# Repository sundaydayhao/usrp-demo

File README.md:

# USRP1 七款子板 KiCad 工程

## Windows 实机诊断与 IQ 采集

2026-09-28 合入本地 Windows 项目的安装、硬件排查和接收实验资料，完整记录见 [Windows 安装与诊断记录](WINDOWS_DIAGNOSTICS.md)。

- `scripts/`：诊断、EEPROM 读取、IQ 采集与离线绘图脚本；Python 依赖见 `requirements.txt`。
- `logs/`：诊断日志、EEPROM 备份、原始 sc16 IQ 数据及采集参数。
- `plots/`：频谱、时频图、CSV 和分析结果。
- `downloads/`：排查时使用的参考源码、原理图、器件资料与 USB 驱动文件。

本地虚拟环境、Python 缓存、UHD 安装包、解压工具目录和上游完整文件列表未提交；这些文件仍保留在本机。原始 IQ 录制及已有的采样溢出、时钟配置等限制详见诊断记录。

## KiCad 子板工程

按用户提供资料重建，每款一个独立工程。BasicRX 与 RXMOD、BasicTX 与 TXMOD 分别合并，不重复交付。所有工程保留 USRP1 接口。

2026-09-14 更新：七个工程的 8 颗 EEPROM 全部改为 **AT24C02（Microchip AT24C02C-SSHM-T / C6203）**，同步原理图、PCB 和 BOM。阻容感支持按价格与供货选择国内或国际品牌；本次锁定 12 颗国巨电阻和 38 颗三星去耦电容。详见 [器件更新说明与采购快照](COMPONENT_UPDATE.md)，EEPROM 页写长度为 8 字节。

| 工程 | 原理图 | PCB | ERC 错误 | DRC 错误 | 未连接 |
|---|---|---|---:|---:|---:|
| [BasicRX](projects/BasicRX/BasicRX.kicad_pro) | [原理图](projects/BasicRX/BasicRX.kicad_sch) | [PCB](projects/BasicRX/BasicRX.kicad_pcb) | 0 | 0 | 0 |
| [BasicTX](projects/BasicTX/BasicTX.kicad_pro) | [原理图](projects/BasicTX/BasicTX.kicad_sch) | [PCB](projects/BasicTX/BasicTX.kicad_pcb) | 0 | 0 | 0 |
| [LFRX](projects/LFRX/LFRX.kicad_pro) | [原理图](projects/LFRX/LFRX.kicad_sch) | [PCB](projects/LFRX/LFRX.kicad_pcb) | 0 | 0 | 0 |
| [LFTX](projects/LFTX/LFTX.kicad_pro) | [原理图](projects/LFTX/LFTX.kicad_sch) | [PCB](projects/LFTX/LFTX.kicad_pcb) | 0 | 0 | 0 |
| [TVRX](projects/TVRX/TVRX.kicad_pro) | [原理图](projects/TVRX/TVRX.kicad_sch) | [PCB](projects/TVRX/TVRX.kicad_pcb) | 0 | 0 | 0 |
| [TVRX2](projects/TVRX2/TVRX2.kicad_pro) | [原理图](projects/TVRX2/TVRX2.kicad_sch) | [PCB](projects/TVRX2/TVRX2.kicad_pcb) | 0 | 0 | 0 |
| [WBX](projects/WBX/WBX.kicad_pro) | [原理图](projects/WBX/WBX.kicad_sch) | [PCB](projects/WBX/WBX.kicad_pcb) | 0 | 0 | 0 |

检查状态来自 `verification/<工程名>/final-summary.json`，只说明 CAD 文件在记录时通过了哪些检查。完整说明见 [DESIGN_NOTES.md](DESIGN_NOTES.md)。

每个目录自带符号、封装、库表、采购 BOM 与预览。用 KiCad 10 打开 `.kicad_pro` 即可编辑。WBX/TVRX2 为按公开资料重新设计的 PCB，射频指标、机械插接和上电功能仍需样板验证；WBX 的 LO 变压器频率裕量、TVRX2 的 CPLD 编程文件尚未通过实物验证。

五款旧板从历史 gEDA CAD 恢复；两款复杂板从 PDF 重建。具体版本、数值差异、器件替代和工艺约束均在设计说明中列出。

WBX 为自定义六层，另外六款为四层；六层的板厂压合与阻抗确认是打样前的必要工作。检查报告保留孤立标签及历史铜线末端等警告，零错误不表示没有警告。

[审查记录](REVIEW.md)列出检查覆盖范围与未验证项目。

## 3D 模型更新

七个工程现有 578 个模型绑定（新增 198 个），全部使用工程内相对路径，并同步至本地封装库。已核对正反面预览，电路和 RF 走线保持不变。PMC 插座与 TVRX 调谐模块采用明确标注的简化外形，机械尺寸限制见 [3D 模型说明](3D_MODELS.md)。

[七款板 3D 预览 PDF](deliverables/3D-previews.pdf) · [完整工程包](deliverables/USRP1-seven-KiCad-projects.zip)

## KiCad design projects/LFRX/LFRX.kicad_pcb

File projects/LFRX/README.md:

# LFRX

低频接收板，保留模拟前端和差分输出滤波网络。

使用 KiCad 10.0.5 验证。打开 `LFRX.kicad_pro`，工程内包含可编辑原理图、PCB、`USRP.kicad_sym`、`USRP.pretty` 和本地库表。多页工程从同名顶层原理图进入。

ERC 错误 0，ERC 警告 6；DRC 错误 0，DRC 警告 8，未连接 0。详见检查报告。

- [采购 BOM](BOM-sourcing.csv)：实际 LCSC 编码仅在已核对型号与封装时填写；空白项仍需选型/询价。
- [预览](preview/)：原理图和 PCB 各铜层图。
- [完整设计说明](../../DESIGN_NOTES.md)：原始资料差异、USRP1 机械接口、RF 匹配、叠层、装配和样板验证限制。
- [检查证据](../../verification/LFRX/)：ERC、DRC、网表、封装与射频检查记录。

必须连同设计说明审查。TVRX2/WBX 使用焊盘内过孔，应评审塞孔盖铜工艺。PCB 上无源器件位号可在 F.Fab/B.Fab 装配层查看。未进行实物功能或射频指标测试。

## 3D 模型

PCB 和本地封装库已绑定工程内的 `3dmodels/`，无需额外安装模型库。请保留整个工程目录。

- [正反面 3D 预览](preview/3d-views.pdf)
- [模型来源、简化模型与尺寸限制](../../3D_MODELS.md)

PMC 插座是简化外形模型；TVRX 的调谐模块也为简化外形，高度按 15 mm 示意，未包含外接 F 连接器。3D 外形补充没有修改电路、焊盘或 RF 走线。

## 2026-09-14 器件更新

EEPROM 已改为 AT24C02，完整料号 Microchip AT24C02C-SSHM-T（C6203）；编程页长 8 字节，不可跨页写入。原有 SOIC-8 焊盘和 3D 模型沿用。阻容感允许按价格、库存和交期选择国内或国际品牌，具体已选料号及待锁定行见本工程 BOM-sourcing.csv；更新证据见 [器件更新说明](../../COMPONENT_UPDATE.md)。

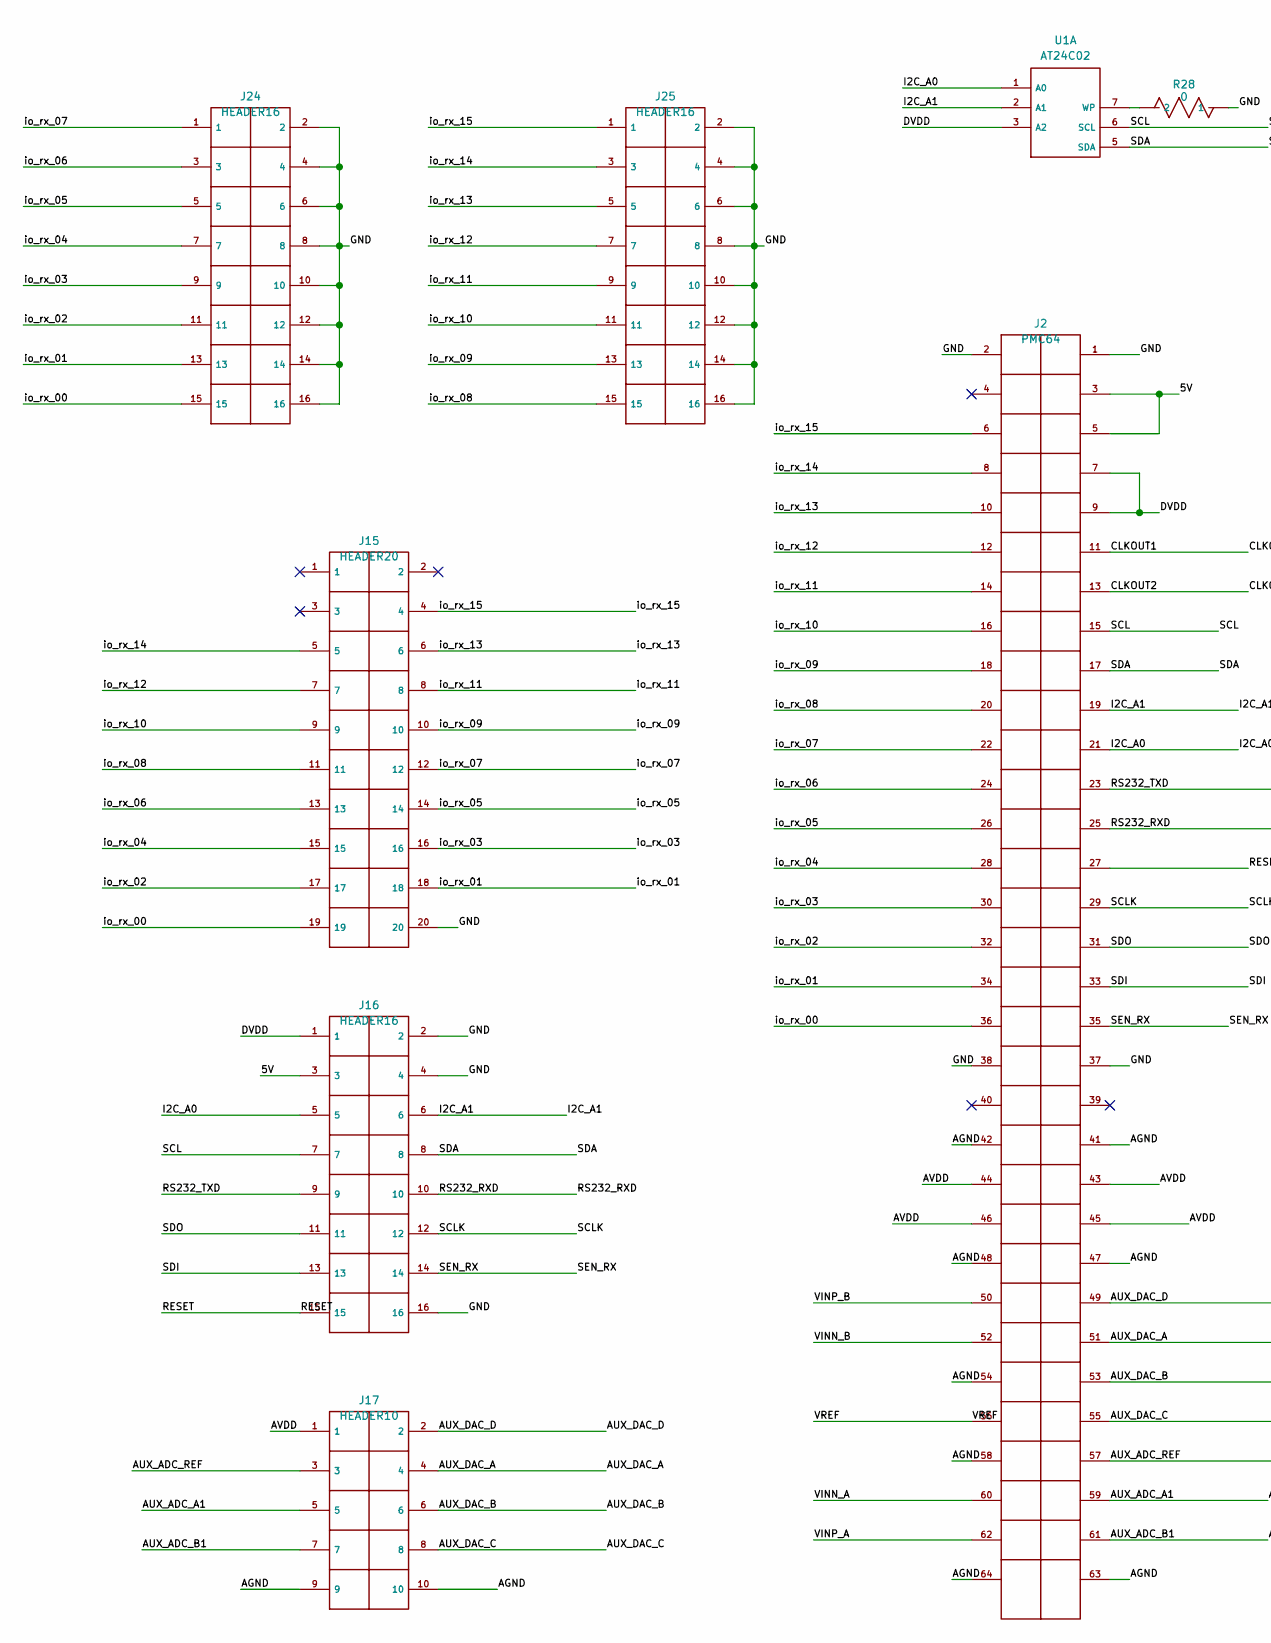
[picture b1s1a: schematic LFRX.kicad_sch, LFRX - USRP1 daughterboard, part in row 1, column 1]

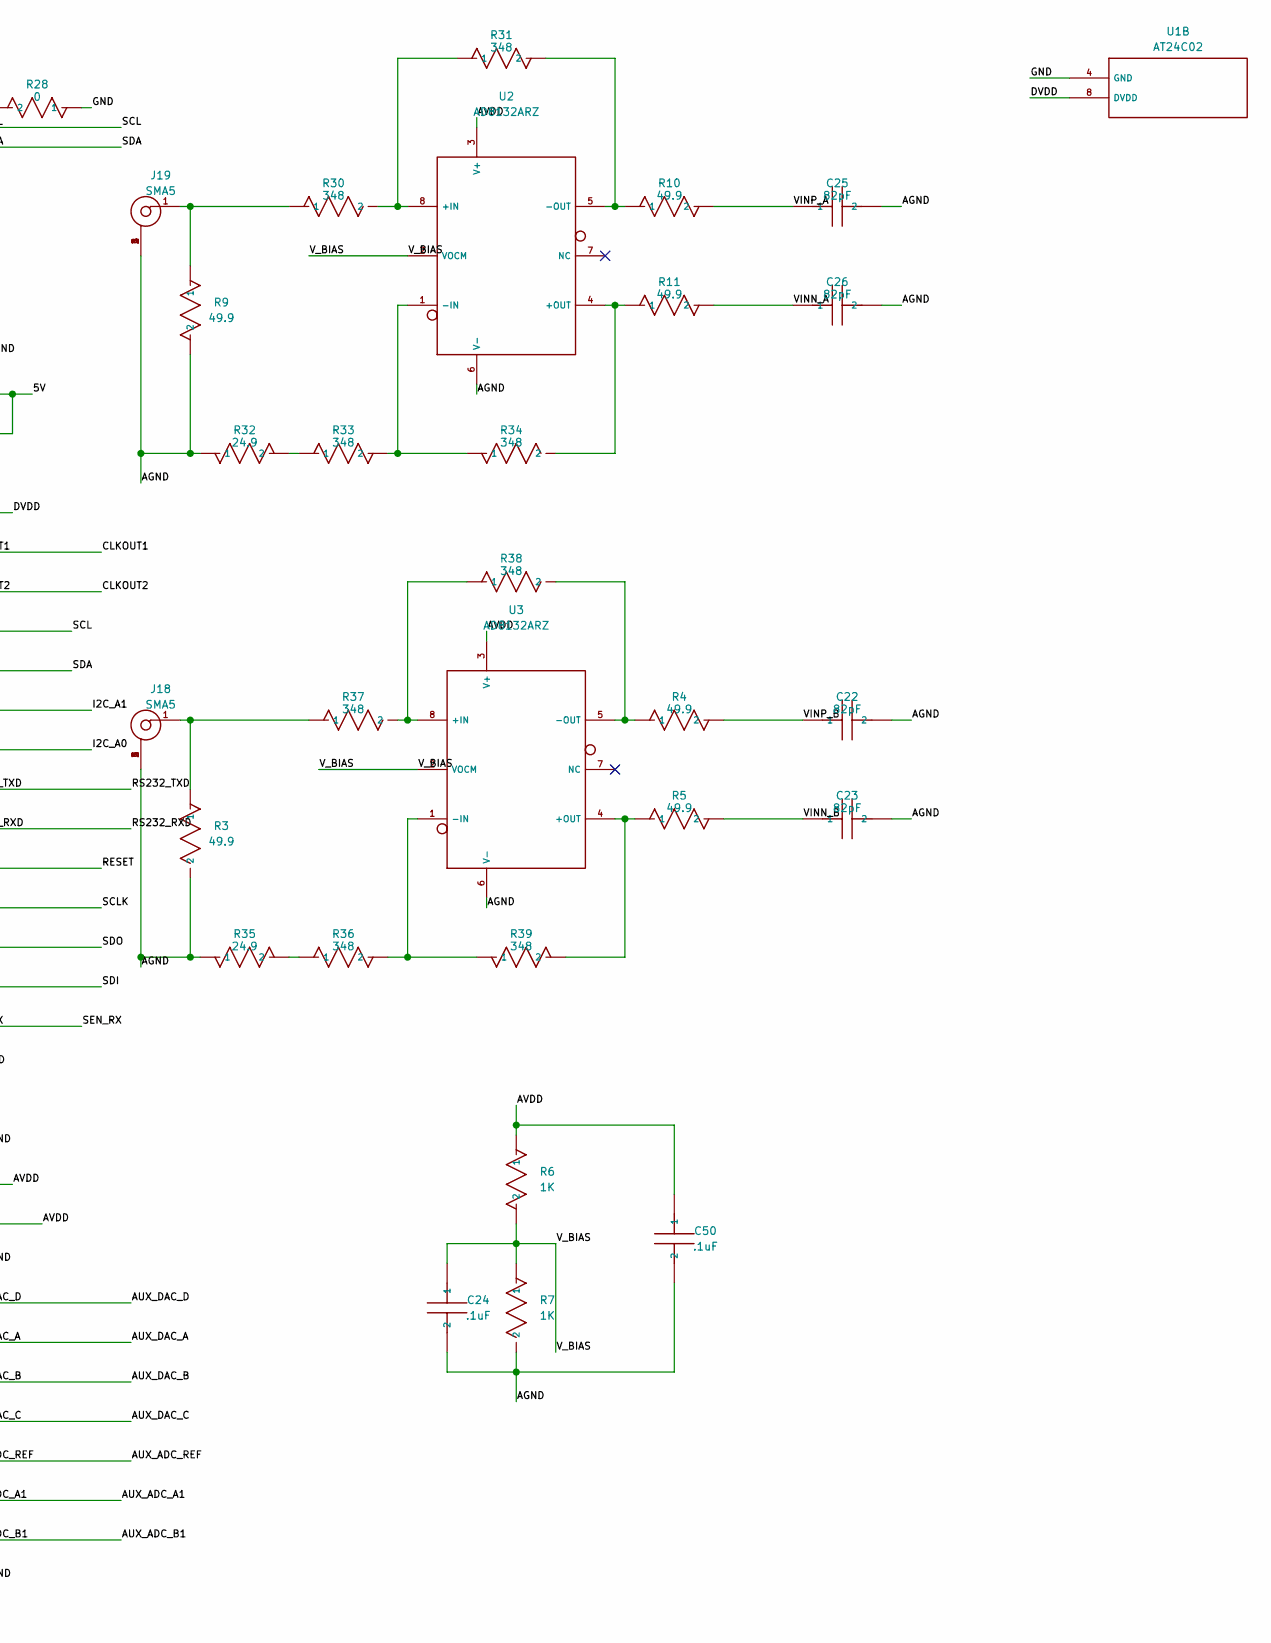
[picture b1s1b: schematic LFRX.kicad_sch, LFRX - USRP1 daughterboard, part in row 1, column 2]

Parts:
C22: 82pF; C22
C23: 82pF; C23
C24: .1uF; C24
C25: 82pF; C25
C26: 82pF; C26
C50: .1uF; C50
J2: PMC64; J2
J15: HEADER20; J15
J16: HEADER16; J16
J17: HEADER10; J17
J18: SMA5; J18
J19: SMA5; J19
J24: HEADER16; J24
J25: HEADER16; J25
R3: 49.9; R3
R4: 49.9; R4
R5: 49.9; R5
R6: 1K; R6
R7: 1K; R7
R9: 49.9; R9
R10: 49.9; R10
R11: 49.9; R11
R28: 0; R28; MPN 0603WAF0000T5E; LCSC C21189
R30: 348; R30
R31: 348; R31
R32: 24.9; R32
R33: 348; R33
R34: 348; R34
R35: 24.9; R35
R36: 348; R36
R37: 348; R37
R38: 348; R38
R39: 348; R39
U1: AT24C02; U1; MPN AT24C02C-SSHM-T; LCSC C6203
U2: AD8132ARZ; U2; MPN AD8132ARZ
U3: AD8132ARZ; U3; MPN AD8132ARZ

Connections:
/5V: J2.3, J2.5, J16.3
/AGND: C22.2, C23.2, C24.2, C25.2, C26.2, C50.2, J2.41, J2.42, J2.47, J2.48, J2.54, J2.58, J2.63, J2.64, J17.9, J17.10, J18.2, J18.3, J18.4, J18.5, J19.2, J19.3, J19.4, J19.5, R3.2, R7.2, R9.2, R32.1, R35.1, U2.6 (V-), U3.6 (V-)
/AUX_ADC_A1: J2.59, J17.5
/AUX_ADC_B1: J2.61, J17.7
/AUX_ADC_REF: J2.57, J17.3
/AUX_DAC_A: J2.51, J17.4
/AUX_DAC_B: J2.53, J17.6
/AUX_DAC_C: J2.55, J17.8
/AUX_DAC_D: J2.49, J17.2
/AVDD: C50.1, J2.43, J2.44, J2.45, J2.46, J17.1, R6.1, U2.3 (V+), U3.3 (V+)
/CLKOUT1: J2.11
/CLKOUT2: J2.13
/DVDD: J2.7, J2.9, J16.1, U1.3 (A2), U1.8 (DVDD)
/GND: J2.1, J2.2, J2.37, J2.38, J15.20, J16.2, J16.4, J16.16, J24.2, J24.4, J24.6, J24.8, J24.10, J24.12, J24.14, J24.16, J25.2, J25.4, J25.6, J25.8, J25.10, J25.12, J25.14, J25.16, R28.1, U1.4 (GND)
/I2C_A0: J2.21, J16.5, U1.1 (A0)
/I2C_A1: J2.19, J16.6, U1.2 (A1)
/RESET: J2.27, J16.15
/RS232_RXD: J2.25, J16.10
/RS232_TXD: J2.23, J16.9
/SCL: J2.15, J16.7, U1.6 (SCL)
/SCLK: J2.29, J16.12
/SDA: J2.17, J16.8, U1.5 (SDA)
/SDI: J2.33, J16.13
/SDO: J2.31, J16.11
/SEN_RX: J2.35, J16.14
/VINN_A: C26.1, J2.60, R11.2
/VINN_B: C23.1, J2.52, R5.2
/VINP_A: C25.1, J2.62, R10.2
/VINP_B: C22.1, J2.50, R4.2
/VREF: J2.56
/V_BIAS: C24.1, R6.2, R7.1, U2.2 (VOCM), U3.2 (VOCM)
/io_rx_00: J2.36, J15.19, J24.15
/io_rx_01: J2.34, J15.18, J24.13
/io_rx_02: J2.32, J15.17, J24.11
/io_rx_03: J2.30, J15.16, J24.9
/io_rx_04: J2.28, J15.15, J24.7
/io_rx_05: J2.26, J15.14, J24.5
/io_rx_06: J2.24, J15.13, J24.3
/io_rx_07: J2.22, J15.12, J24.1
/io_rx_08: J2.20, J15.11, J25.15
/io_rx_09: J2.18, J15.10, J25.13
/io_rx_10: J2.16, J15.9, J25.11
/io_rx_11: J2.14, J15.8, J25.9
/io_rx_12: J2.12, J15.7, J25.7
/io_rx_13: J2.10, J15.6, J25.5
/io_rx_14: J2.8, J15.5, J25.3
/io_rx_15: J2.6, J15.4, J25.1
unnamed: J18.1, R3.1, R37.1
unnamed: J19.1, R9.1, R30.1
unnamed: R32.2, R33.1
unnamed: R35.2, R36.1
unnamed: R28.2, U1.7 (WP)
unnamed: R30.2, R31.1, U2.8 (+IN)
unnamed: R11.1, R34.2, U2.4 (+OUT)
unnamed: R33.2, R34.1, U2.1 (-IN)
unnamed: R10.1, R31.2, U2.5 (-OUT)
unnamed: R37.2, R38.1, U3.8 (+IN)
unnamed: R5.1, R39.2, U3.4 (+OUT)
unnamed: R36.2, R39.1, U3.1 (-IN)
unnamed: R4.1, R38.2, U3.5 (-OUT)

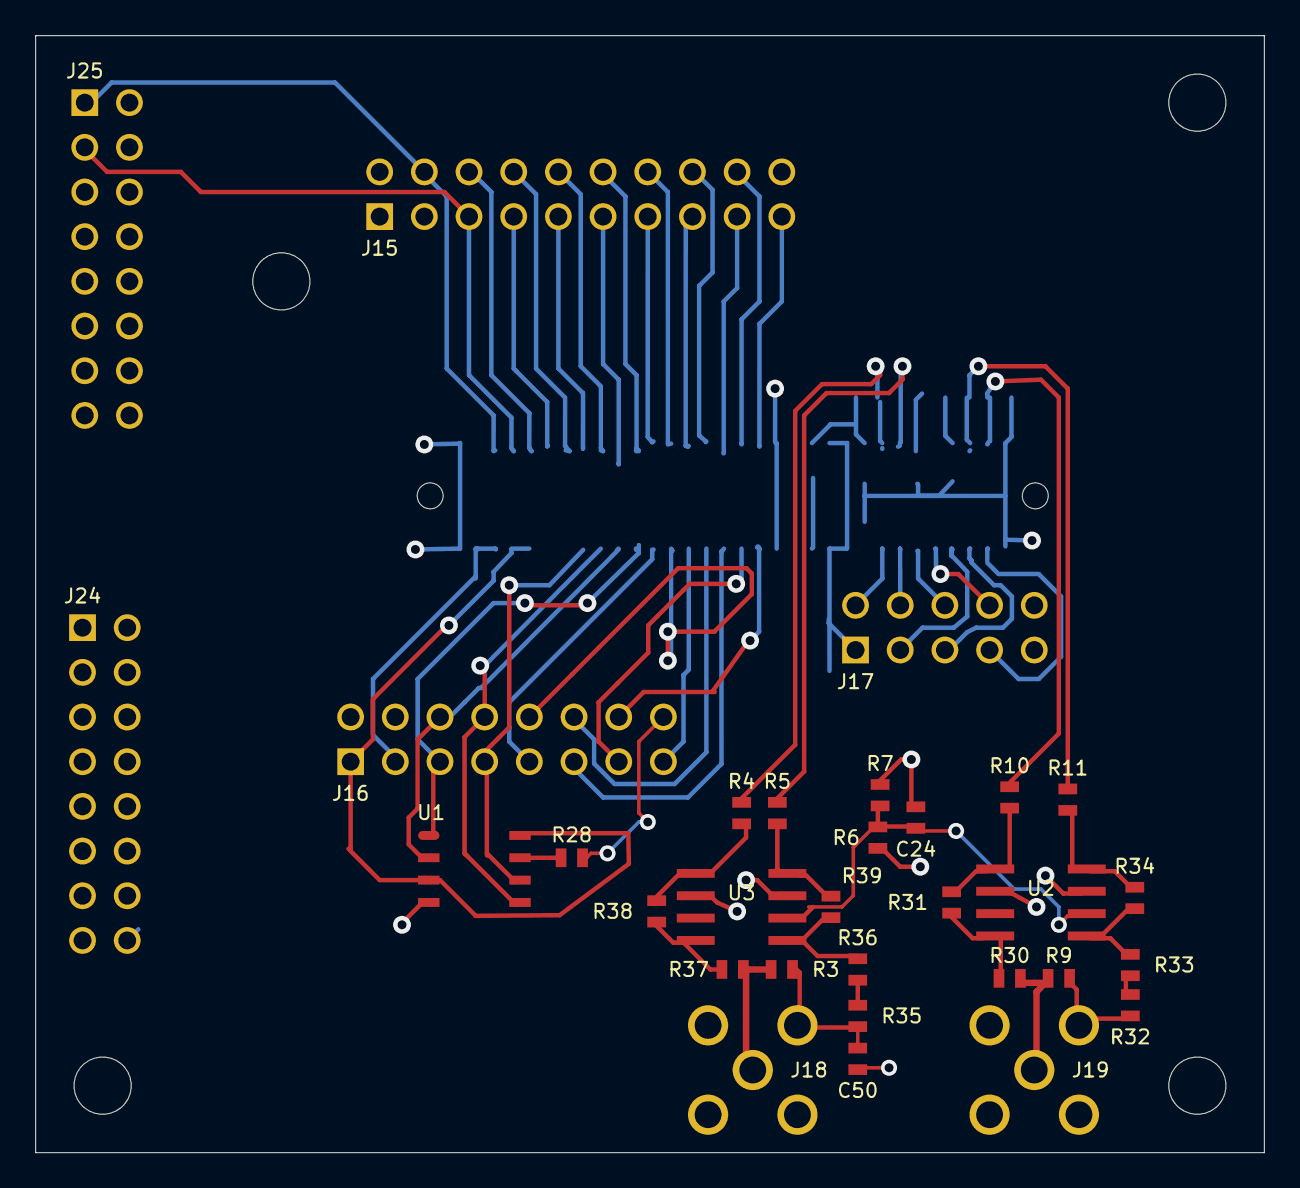
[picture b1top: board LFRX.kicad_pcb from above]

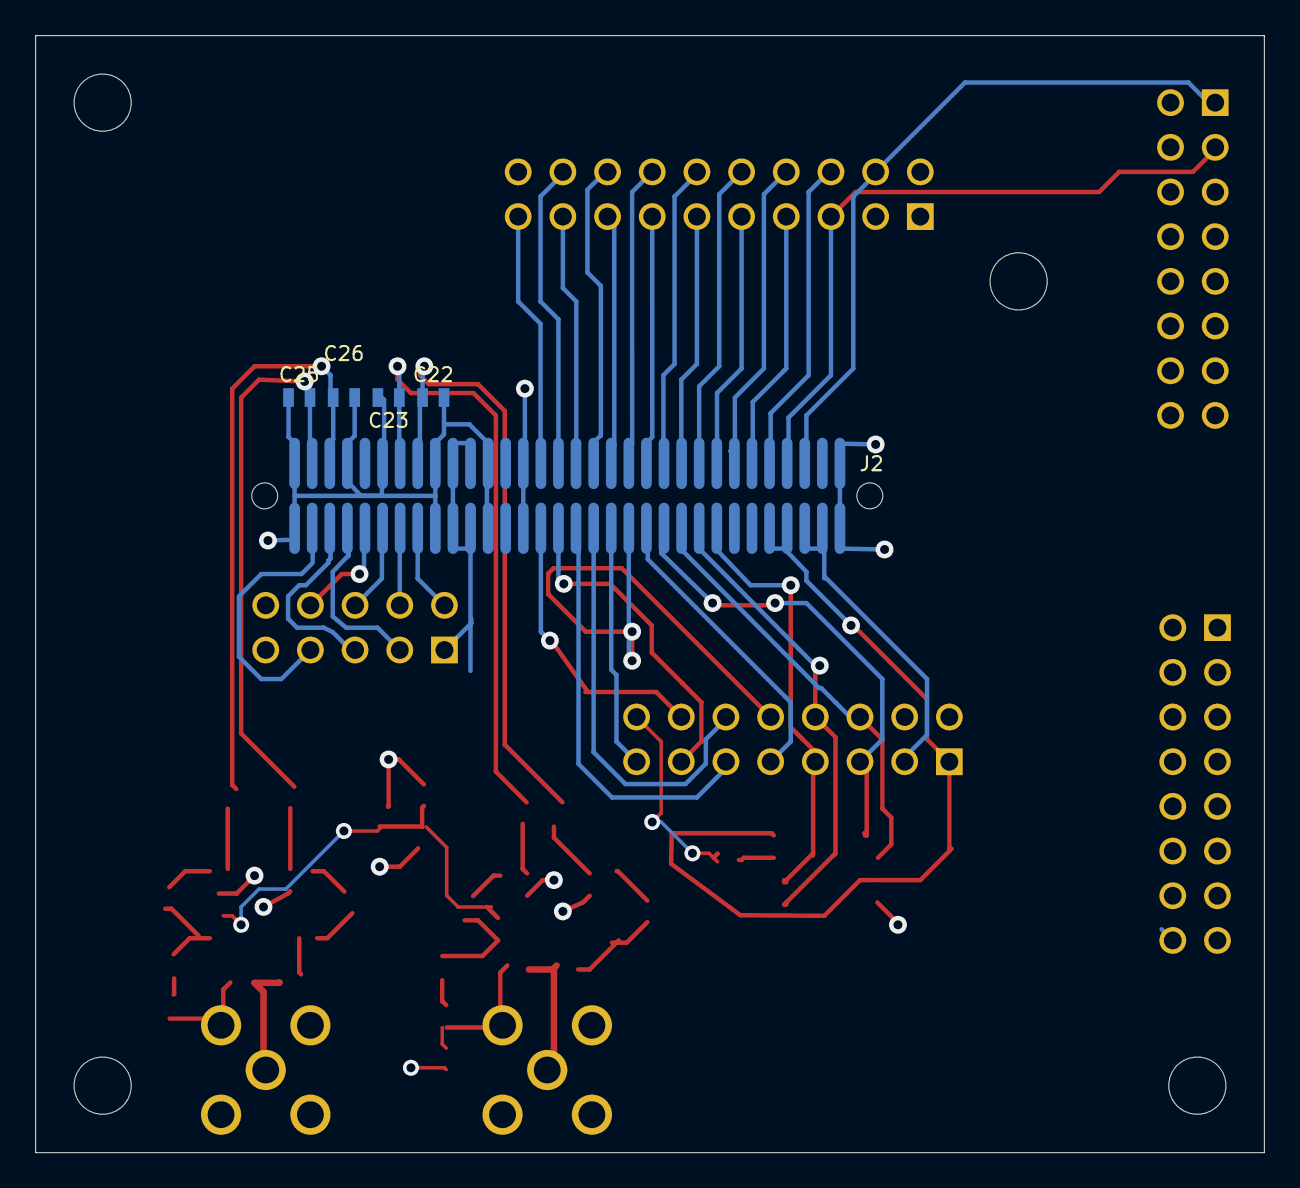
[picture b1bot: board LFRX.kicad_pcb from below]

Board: 4 copper layers, 69.8 x 63.5 mm, 40 parts (5 on the bottom side), 57 nets.

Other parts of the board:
H1, H2, H3, H4: NPTH

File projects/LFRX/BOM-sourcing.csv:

Reference,Value,Footprint,Manufacturer,MPN,LCSC,Sourcing_status,Specification,Source_value,Evidence,Approved_brands,Sourcing_policy
C22,82pF,USRP:C22,候选：Murata / TDK / Samsung Electro-Mechanics / Walsin / FH / EYANG,,,规格选型，待锁定料号,按项目焊盘尺寸；RF/匹配/PLL环路优先 C0G；去耦 X7R；耐压 >=16 V；保留原容差,82pF,,Murata / TDK / Samsung Electro-Mechanics / Walsin / FH / EYANG,国产与国际品牌均可；满足参数后比较含税到手价、起订量、库存和交期；换料须复核封装及电气指标
C23,82pF,USRP:C23,候选：Murata / TDK / Samsung Electro-Mechanics / Walsin / FH / EYANG,,,规格选型，待锁定料号,按项目焊盘尺寸；RF/匹配/PLL环路优先 C0G；去耦 X7R；耐压 >=16 V；保留原容差,82pF,,Murata / TDK / Samsung Electro-Mechanics / Walsin / FH / EYANG,国产与国际品牌均可；满足参数后比较含税到手价、起订量、库存和交期；换料须复核封装及电气指标
C24,.1uF,USRP:C24,候选：Murata / TDK / Samsung Electro-Mechanics / Walsin / FH / EYANG,,,规格选型，待锁定料号,按项目焊盘尺寸；RF/匹配/PLL环路优先 C0G；去耦 X7R；耐压 >=16 V；保留原容差,.1uF,,Murata / TDK / Samsung Electro-Mechanics / Walsin / FH / EYANG,国产与国际品牌均可；满足参数后比较含税到手价、起订量、库存和交期；换料须复核封装及电气指标
C25,82pF,USRP:C25,候选：Murata / TDK / Samsung Electro-Mechanics / Walsin / FH / EYANG,,,规格选型，待锁定料号,按项目焊盘尺寸；RF/匹配/PLL环路优先 C0G；去耦 X7R；耐压 >=16 V；保留原容差,82pF,,Murata / TDK / Samsung Electro-Mechanics / Walsin / FH / EYANG,国产与国际品牌均可；满足参数后比较含税到手价、起订量、库存和交期；换料须复核封装及电气指标
C26,82pF,USRP:C26,候选：Murata / TDK / Samsung Electro-Mechanics / Walsin / FH / EYANG,,,规格选型，待锁定料号,按项目焊盘尺寸；RF/匹配/PLL环路优先 C0G；去耦 X7R；耐压 >=16 V；保留原容差,82pF,,Murata / TDK / Samsung Electro-Mechanics / Walsin / FH / EYANG,国产与国际品牌均可；满足参数后比较含税到手价、起订量、库存和交期；换料须复核封装及电气指标
C50,.1uF,USRP:C50,候选：Murata / TDK / Samsung Electro-Mechanics / Walsin / FH / EYANG,,,规格选型，待锁定料号,按项目焊盘尺寸；RF/匹配/PLL环路优先 C0G；去耦 X7R；耐压 >=16 V；保留原容差,.1uF,,Murata / TDK / Samsung Electro-Mechanics / Walsin / FH / EYANG,国产与国际品牌均可；满足参数后比较含税到手价、起订量、库存和交期；换料须复核封装及电气指标
J2,PMC64,USRP:J2,,,,规格选型，待锁定料号,按工程封装和 USRP1 接口核对插合方向、针脚与高度,PMC64,,,
J15,HEADER20,USRP:J15,,,,规格选型，待锁定料号,按工程封装和 USRP1 接口核对插合方向、针脚与高度,HEADER20,,,
J16,HEADER16,USRP:J16,,,,规格选型，待锁定料号,按工程封装和 USRP1 接口核对插合方向、针脚与高度,HEADER16,,,
J17,HEADER10,USRP:J17,,,,规格选型，待锁定料号,按工程封装和 USRP1 接口核对插合方向、针脚与高度,HEADER10,,,
J18,SMA5,USRP:J18,,,,规格选型，待锁定料号,按工程封装和 USRP1 接口核对插合方向、针脚与高度,SMA5,,,
J19,SMA5,USRP:J19,,,,规格选型，待锁定料号,按工程封装和 USRP1 接口核对插合方向、针脚与高度,SMA5,,,
J24,HEADER16,USRP:J24,,,,规格选型，待锁定料号,按工程封装和 USRP1 接口核对插合方向、针脚与高度,HEADER16,,,
J25,HEADER16,USRP:J25,,,,规格选型，待锁定料号,按工程封装和 USRP1 接口核对插合方向、针脚与高度,HEADER16,,,
R3,49.9,USRP:R3,候选：YAGEO / Vishay / Panasonic / UNI-ROYAL / FH,,,规格选型，待锁定料号,0603; <=1%; >=0.1 W; 按原值采购；反馈/终端电阻需同批次,49.9,,YAGEO / Vishay / Panasonic / UNI-ROYAL / FH,国产与国际品牌均可；满足参数后比较含税到手价、起订量、库存和交期；换料须复核封装及电气指标
R4,49.9,USRP:R4,候选：YAGEO / Vishay / Panasonic / UNI-ROYAL / FH,,,规格选型，待锁定料号,0603; <=1%; >=0.1 W; 按原值采购；反馈/终端电阻需同批次,49.9,,YAGEO / Vishay / Panasonic / UNI-ROYAL / FH,国产与国际品牌均可；满足参数后比较含税到手价、起订量、库存和交期；换料须复核封装及电气指标
R5,49.9,USRP:R5,候选：YAGEO / Vishay / Panasonic / UNI-ROYAL / FH,,,规格选型，待锁定料号,0603; <=1%; >=0.1 W; 按原值采购；反馈/终端电阻需同批次,49.9,,YAGEO / Vishay / Panasonic / UNI-ROYAL / FH,国产与国际品牌均可；满足参数后比较含税到手价、起订量、库存和交期；换料须复核封装及电气指标
R6,1K,USRP:R6,候选：YAGEO / Vishay / Panasonic / UNI-ROYAL / FH,,,规格选型，待锁定料号,0603; <=1%; >=0.1 W; 按原值采购；反馈/终端电阻需同批次,1K,,YAGEO / Vishay / Panasonic / UNI-ROYAL / FH,国产与国际品牌均可；满足参数后比较含税到手价、起订量、库存和交期；换料须复核封装及电气指标
R7,1K,USRP:R7,候选：YAGEO / Vishay / Panasonic / UNI-ROYAL / FH,,,规格选型，待锁定料号,0603; <=1%; >=0.1 W; 按原值采购；反馈/终端电阻需同批次,1K,,YAGEO / Vishay / Panasonic / UNI-ROYAL / FH,国产与国际品牌均可；满足参数后比较含税到手价、起订量、库存和交期；换料须复核封装及电气指标
R9,49.9,USRP:R9,候选：YAGEO / Vishay / Panasonic / UNI-ROYAL / FH,,,规格选型，待锁定料号,0603; <=1%; >=0.1 W; 按原值采购；反馈/终端电阻需同批次,49.9,,YAGEO / Vishay / Panasonic / UNI-ROYAL / FH,国产与国际品牌均可；满足参数后比较含税到手价、起订量、库存和交期；换料须复核封装及电气指标
R10,49.9,USRP:R10,候选：YAGEO / Vishay / Panasonic / UNI-ROYAL / FH,,,规格选型，待锁定料号,0603; <=1%; >=0.1 W; 按原值采购；反馈/终端电阻需同批次,49.9,,YAGEO / Vishay / Panasonic / UNI-ROYAL / FH,国产与国际品牌均可；满足参数后比较含税到手价、起订量、库存和交期；换料须复核封装及电气指标
R11,49.9,USRP:R11,候选：YAGEO / Vishay / Panasonic / UNI-ROYAL / FH,,,规格选型，待锁定料号,0603; <=1%; >=0.1 W; 按原值采购；反馈/终端电阻需同批次,49.9,,YAGEO / Vishay / Panasonic / UNI-ROYAL / FH,国产与国际品牌均可；满足参数后比较含税到手价、起订量、库存和交期；换料须复核封装及电气指标
R28,0,USRP:R28,UNI-ROYAL 厚声,0603WAF0000T5E,C21189,已核对目录料号,0603; <=1%; >=0.1 W; 按原值采购；反馈/终端电阻需同批次,0,https://www.lcsc.com/product-detail/C21189.html,YAGEO / Vishay / Panasonic / UNI-ROYAL / FH,国产与国际品牌均可；满足参数后比较含税到手价、起订量、库存和交期；换料须复核封装及电气指标
R30,348,USRP:R30,候选：YAGEO / Vishay / Panasonic / UNI-ROYAL / FH,,,规格选型，待锁定料号,0603; <=1%; >=0.1 W; 按原值采购；反馈/终端电阻需同批次,348,,YAGEO / Vishay / Panasonic / UNI-ROYAL / FH,国产与国际品牌均可；满足参数后比较含税到手价、起订量、库存和交期；换料须复核封装及电气指标
R31,348,USRP:R31,候选：YAGEO / Vishay / Panasonic / UNI-ROYAL / FH,,,规格选型，待锁定料号,0603; <=1%; >=0.1 W; 按原值采购；反馈/终端电阻需同批次,348,,YAGEO / Vishay / Panasonic / UNI-ROYAL / FH,国产与国际品牌均可；满足参数后比较含税到手价、起订量、库存和交期；换料须复核封装及电气指标
R32,24.9,USRP:R32,候选：YAGEO / Vishay / Panasonic / UNI-ROYAL / FH,,,规格选型，待锁定料号,0603; <=1%; >=0.1 W; 按原值采购；反馈/终端电阻需同批次,24.9,,YAGEO / Vishay / Panasonic / UNI-ROYAL / FH,国产与国际品牌均可；满足参数后比较含税到手价、起订量、库存和交期；换料须复核封装及电气指标
R33,348,USRP:R33,候选：YAGEO / Vishay / Panasonic / UNI-ROYAL / FH,,,规格选型，待锁定料号,0603; <=1%; >=0.1 W; 按原值采购；反馈/终端电阻需同批次,348,,YAGEO / Vishay / Panasonic / UNI-ROYAL / FH,国产与国际品牌均可；满足参数后比较含税到手价、起订量、库存和交期；换料须复核封装及电气指标
R34,348,USRP:R34,候选：YAGEO / Vishay / Panasonic / UNI-ROYAL / FH,,,规格选型，待锁定料号,0603; <=1%; >=0.1 W; 按原值采购；反馈/终端电阻需同批次,348,,YAGEO / Vishay / Panasonic / UNI-ROYAL / FH,国产与国际品牌均可；满足参数后比较含税到手价、起订量、库存和交期；换料须复核封装及电气指标
R35,24.9,USRP:R35,候选：YAGEO / Vishay / Panasonic / UNI-ROYAL / FH,,,规格选型，待锁定料号,0603; <=1%; >=0.1 W; 按原值采购；反馈/终端电阻需同批次,24.9,,YAGEO / Vishay / Panasonic / UNI-ROYAL / FH,国产与国际品牌均可；满足参数后比较含税到手价、起订量、库存和交期；换料须复核封装及电气指标
R36,348,USRP:R36,候选：YAGEO / Vishay / Panasonic / UNI-ROYAL / FH,,,规格选型，待锁定料号,0603; <=1%; >=0.1 W; 按原值采购；反馈/终端电阻需同批次,348,,YAGEO / Vishay / Panasonic / UNI-ROYAL / FH,国产与国际品牌均可；满足参数后比较含税到手价、起订量、库存和交期；换料须复核封装及电气指标
R37,348,USRP:R37,候选：YAGEO / Vishay / Panasonic / UNI-ROYAL / FH,,,规格选型，待锁定料号,0603; <=1%; >=0.1 W; 按原值采购；反馈/终端电阻需同批次,348,,YAGEO / Vishay / Panasonic / UNI-ROYAL / FH,国产与国际品牌均可；满足参数后比较含税到手价、起订量、库存和交期；换料须复核封装及电气指标
R38,348,USRP:R38,候选：YAGEO / Vishay / Panasonic / UNI-ROYAL / FH,,,规格选型，待锁定料号,0603; <=1%; >=0.1 W; 按原值采购；反馈/终端电阻需同批次,348,,YAGEO / Vishay / Panasonic / UNI-ROYAL / FH,国产与国际品牌均可；满足参数后比较含税到手价、起订量、库存和交期；换料须复核封装及电气指标
R39,348,USRP:R39,候选：YAGEO / Vishay / Panasonic / UNI-ROYAL / FH,,,规格选型，待锁定料号,0603; <=1%; >=0.1 W; 按原值采购；反馈/终端电阻需同批次,348,,YAGEO / Vishay / Panasonic / UNI-ROYAL / FH,国产与国际品牌均可；满足参数后比较含税到手价、起订量、库存和交期；换料须复核封装及电气指标
U1,AT24C02,USRP:U1,Microchip,AT24C02C-SSHM-T,C6203,已核对引脚/封装/电压/目录；8-byte页写；待实机写入及识别,"SOIC-8 3.9x4.9 mm, P1.27 mm; 1.7–5.5 V; 2 Kbit (256x8); 8-byte page; WP=0; write <=5 ms; ACK polling; 不跨8字节页边界",24LC025B,https://ww1.microchip.com/downloads/en/DeviceDoc/AT24C01C-AT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,Microchip,按完整MPN和厂家采购，不能仅按AT24C02通用名下单
U2,AD8132ARZ,USRP:U2,,AD8132ARZ,,保留原功能型号；采购需核对后缀、封装与供应状态,射频/高速/低噪声器件，不作未经验证的国产等效替换,AD813X,,,
U3,AD8132ARZ,USRP:U3,,AD8132ARZ,,保留原功能型号；采购需核对后缀、封装与供应状态,射频/高速/低噪声器件，不作未经验证的国产等效替换,AD813X,,,

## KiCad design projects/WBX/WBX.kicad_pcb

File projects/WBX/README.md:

# WBX

旧版 ADL5386/ADL5387 宽带收发板；默认 SMA 装配，保留两个 USRP1 接插件。

使用 KiCad 10.0.5 验证。打开 `WBX.kicad_pro`，工程内包含可编辑原理图、PCB、`USRP.kicad_sym`、`USRP.pretty` 和本地库表。多页工程从同名顶层原理图进入。

ERC 错误 0，ERC 警告 6；DRC 错误 0，DRC 警告 22，未连接 0。详见检查报告。

- [采购 BOM](BOM-sourcing.csv)：实际 LCSC 编码仅在已核对型号与封装时填写；空白项仍需选型/询价。
- [预览](preview/)：原理图和 PCB 各铜层图。
- [完整设计说明](../../DESIGN_NOTES.md)：原始资料差异、USRP1 机械接口、RF 匹配、叠层、装配和样板验证限制。
- [检查证据](../../verification/WBX/)：ERC、DRC、网表、封装与射频检查记录。

必须连同设计说明审查。TVRX2/WBX 使用焊盘内过孔，应评审塞孔盖铜工艺。PCB 上无源器件位号可在 F.Fab/B.Fab 装配层查看。未进行实物功能或射频指标测试。

## 3D 模型

PCB 和本地封装库已绑定工程内的 `3dmodels/`，无需额外安装模型库。请保留整个工程目录。

- [正反面 3D 预览](preview/3d-views.pdf)
- [模型来源、简化模型与尺寸限制](../../3D_MODELS.md)

PMC 插座是简化外形模型；TVRX 的调谐模块也为简化外形，高度按 15 mm 示意，未包含外接 F 连接器。3D 外形补充没有修改电路、焊盘或 RF 走线。

## 2026-09-14 器件更新

EEPROM 已改为 AT24C02，完整料号 Microchip AT24C02C-SSHM-T（C6203）；编程页长 8 字节，不可跨页写入。原有 SOIC-8 焊盘和 3D 模型沿用。阻容感允许按价格、库存和交期选择国内或国际品牌，具体已选料号及待锁定行见本工程 BOM-sourcing.csv；更新证据见 [器件更新说明](../../COMPONENT_UPDATE.md)。

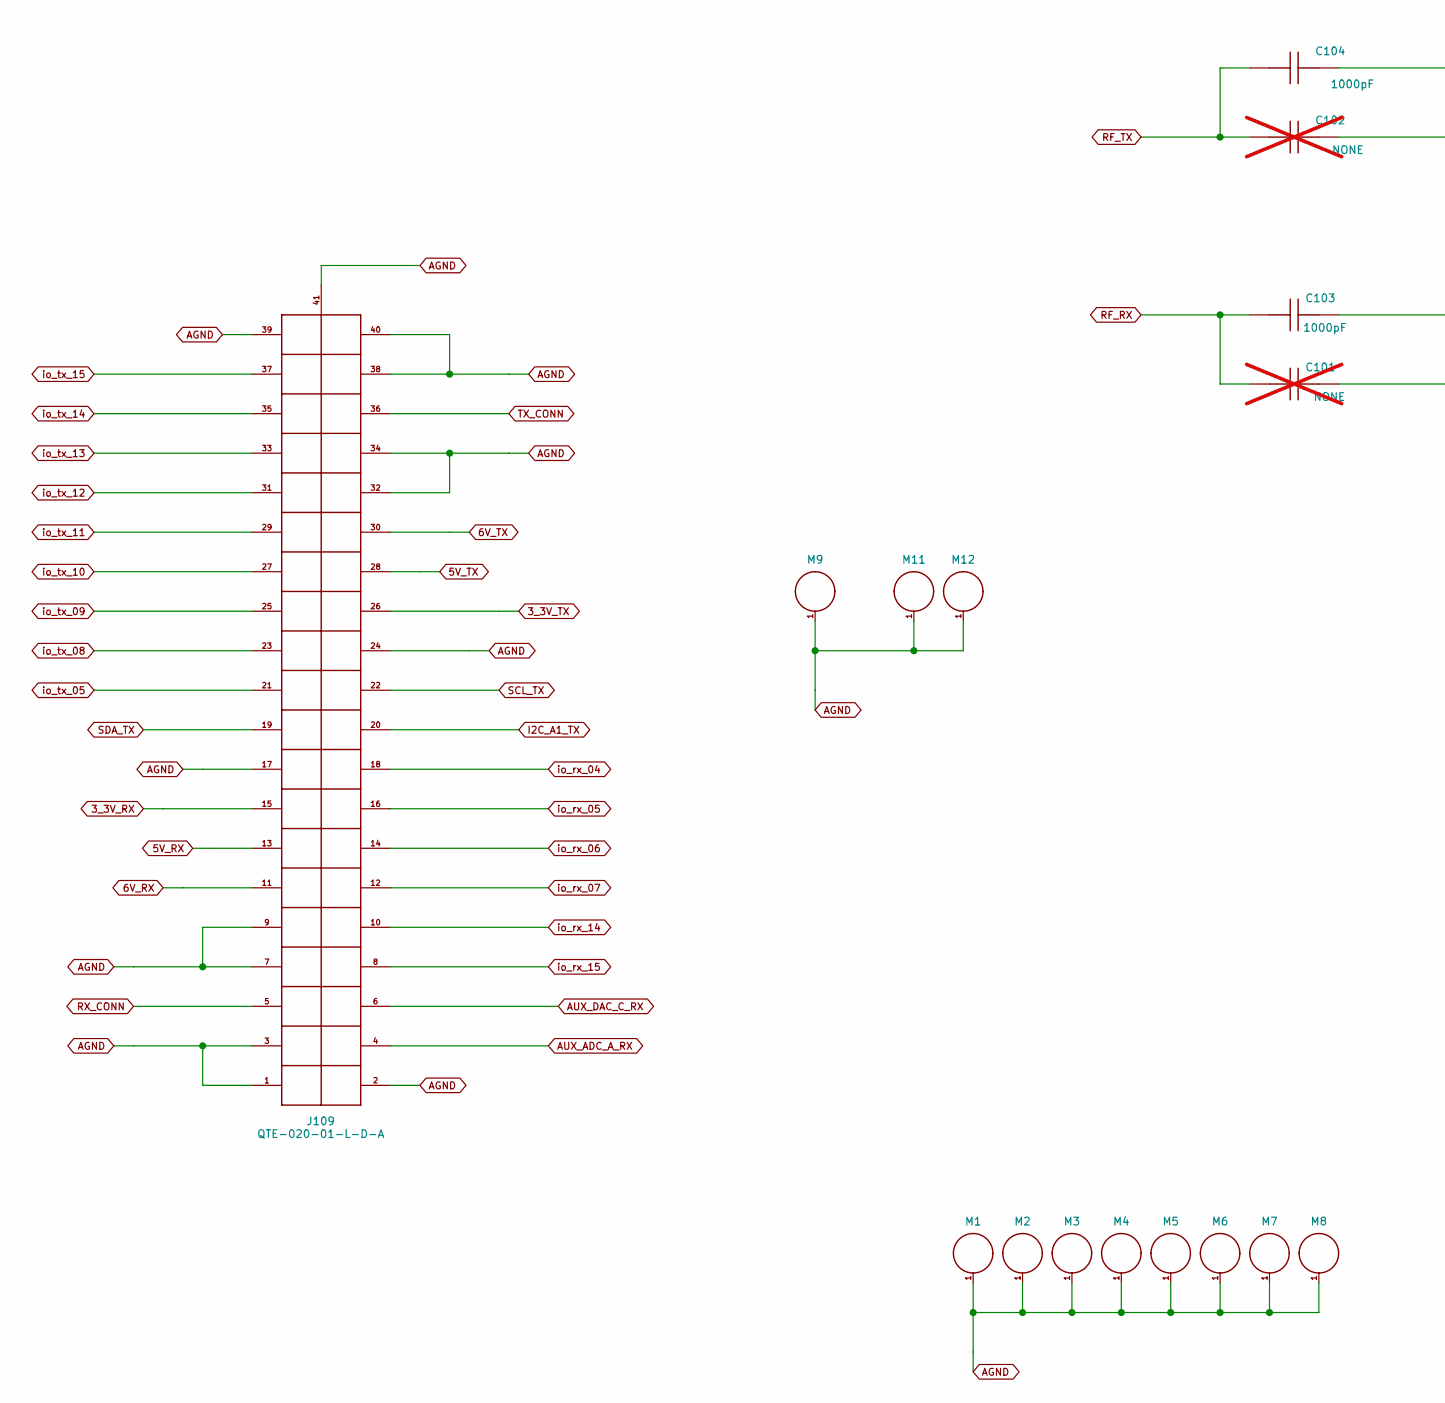
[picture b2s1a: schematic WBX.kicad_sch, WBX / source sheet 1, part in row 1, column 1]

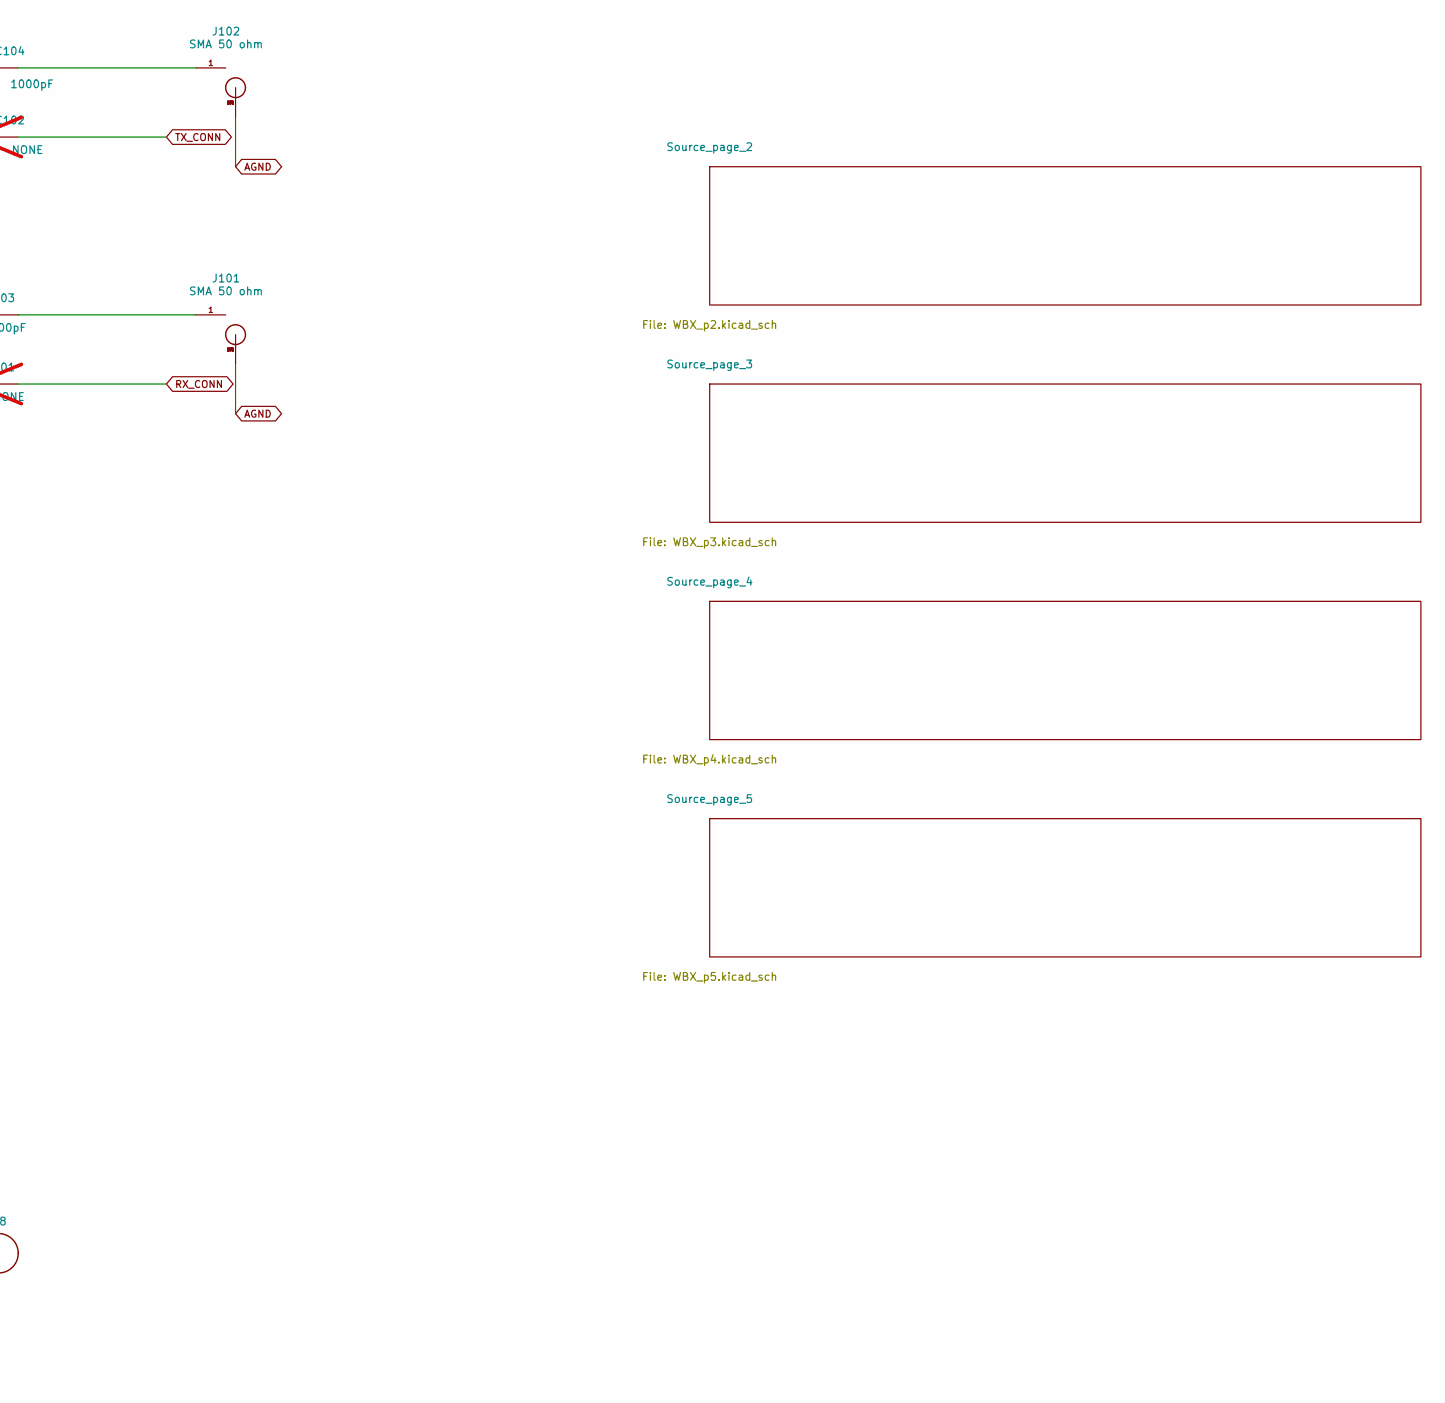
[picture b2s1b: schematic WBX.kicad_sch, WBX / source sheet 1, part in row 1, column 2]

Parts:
C101: NONE; C101; not fitted
C102: NONE; C102; not fitted
C103: 1000pF; C103
C104: 1000pF; C104
J101: SMA 50 ohm; J101
J102: SMA 50 ohm; J102
J109: QTE-020-01-L-D-A; J109
M1: M2.5 GND; M1
M2: M2.5 GND; M2
M3: M2.5 GND; M3
M4: M2.5 GND; M4
M5: M2.5 GND; M5
M6: M2.5 GND; M6
M7: M2.5 GND; M7
M8: M2.5 GND; M8
M9: M2.5 GND; M9
M11: M2.5 GND; M11
M12: M2.5 GND; M12

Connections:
3_3V_RX: J109.15; also elsewhere on the board
3_3V_TX: J109.26; also elsewhere on the board
5V_RX: J109.13; also elsewhere on the board
5V_TX: J109.28; also elsewhere on the board
6V_RX: J109.11; also elsewhere on the board
6V_TX: J109.30; also elsewhere on the board
AGND: J101.2, J101.3, J101.4, J101.5, J102.2, J102.3, J102.4, J102.5, J109.1, J109.2, J109.3, J109.7, J109.9, J109.17, J109.24, J109.32, J109.34, J109.38, J109.39, J109.40, J109.41, M1.1, M2.1, M3.1, M4.1, M5.1, M6.1, M7.1, M8.1, M9.1, M11.1, M12.1; also elsewhere on the board
AUX_ADC_A_RX: J109.4; also elsewhere on the board
AUX_DAC_C_RX: J109.6; also elsewhere on the board
I2C_A1_TX: J109.20; also elsewhere on the board
unnamed: C103.1, J101.1
unnamed: C104.1, J102.1
RF_RX: C101.2, C103.2; also elsewhere on the board
RF_TX: C102.2, C104.2; also elsewhere on the board
RX_CONN: C101.1, J109.5
SCL_TX: J109.22; also elsewhere on the board
SDA_TX: J109.19; also elsewhere on the board
TX_CONN: C102.1, J109.36
io_rx_04: J109.18; also elsewhere on the board
io_rx_05: J109.16; also elsewhere on the board
io_rx_06: J109.14; also elsewhere on the board
io_rx_07: J109.12; also elsewhere on the board
io_rx_14: J109.10; also elsewhere on the board
io_rx_15: J109.8; also elsewhere on the board
io_tx_05: J109.21; also elsewhere on the board
io_tx_08: J109.23; also elsewhere on the board
io_tx_09: J109.25; also elsewhere on the board
io_tx_10: J109.27; also elsewhere on the board
io_tx_11: J109.29; also elsewhere on the board
io_tx_12: J109.31; also elsewhere on the board
io_tx_13: J109.33; also elsewhere on the board
io_tx_14: J109.35; also elsewhere on the board
io_tx_15: J109.37; also elsewhere on the board

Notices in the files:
projects/LFRX/LFRX.kicad_pcb:
(c) 2006 Ettus Research LLC
